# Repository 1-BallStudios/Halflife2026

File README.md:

## Hello!
This is my Starbie.
As the description says, this is "a tiny motion-controlled digital pet, basically a desktop Tamagotchi."

I don't exactly know what to do with how to flash the firmware (**SINCE I DONT HAVE IT YET**), but assembling it should be pretty simple with the parts.

## I'm just using the example because idc
1. Clone the source code to your device
```sh
git clone https://github.com/1-BallStudios/Halflife2026.git
```

2. Install the project's dependencies
```sh
npm install
```

3. Start the development server on `localhost:xxxx`
```sh
npm run dev
```

4. Build the site to `/dist`
```sh
npm run build
```

This project was made almost entirely using the Starbie Week 1 Guide: [Here it is!](https://github.com/SharKingStudios/Starbie/blob/main/Week%201%20Guide.md)
*the thing is... i have almost no idea what im doing. :(* At least I'm learning! :]

## ALSO
When I rendered it, the XIAO-ESPC3 looked fine when I viewed it separately, but in the final render it's not there for some reason. Weird!

# Starbie – bill of materials [PCB Isn't in here]

| Week | Tier | Parts funding |
| --- | --- | --- |
| Week 1 | Tier 1 | $30.00 |

| Part | What it's for | Qty | Unit | Total | Vendor |
| --- | --- | --- | --- | --- | --- |
| [XIAO-ESP32-C3-SMD](https://www.aliexpress.us/item/3256806898073871.html) | Main Microprocessor | 1 | $2.95 | $2.95 | [AliExpress](https://www.aliexpress.us/item/3256806898073871.html) |
| [Push Button Switch](https://www.walmart.com/ip/3x6x3-5mm-Momentary-Tact-Tactile-Push-Button-Switch-Surface-Mounted-Devices-SMT-PCB-2-Pin-50Pcs/922165931?wmlspartner=wlpa&selectedSellerId=571) | Buttons (SORRY THIS IS A 50-PACK) | 2 | $0.44 | $0.88 | [Walmart](https://www.walmart.com/ip/3x6x3-5mm-Momentary-Tact-Tactile-Push-Button-Switch-Surface-Mounted-Devices-SMT-PCB-2-Pin-50Pcs/922165931?wmlspartner=wlpa&selectedSellerId=571) |
| [DHT11 Module](https://www.aliexpress.com/item/32840892862.html) | Enviornment Sensor i think | 1 | $0.44 | $0.44 | [AliExpress](https://www.aliexpress.com/item/32840892862.html) |
| [10kΩ Resistor](https://vetco.net/products/nte-qw310_10k_ohm_1-4_watt_resistor?variant=42879213928585&_gsid=cyqQckRv9BK9) | Resistor | 1 | $0.29 | $0.29 | [Vetco Electronics](https://vetco.net/products/nte-qw310_10k_ohm_1-4_watt_resistor?variant=42879213928585&_gsid=cyqQckRv9BK9) |
| [1.3" OLED Display](https://www.aliexpress.com/item/1005006862867338.html) | Screen | 1 | $0.99 | $0.99 | [AliExpress](https://www.aliexpress.com/item/1005006862867338.html) |
| [MPU6050 Module](https://www.aliexpress.com/w/wholesale-MPU6050.html) | Movement Sensor i think | 1 | $1.09 | $1.09 | [AliExpress](https://www.aliexpress.com/w/wholesale-MPU6050.html) |
| **Parts subtotal** | — | — | — | **$6.64** | — |
| **Tax & shipping** | — | — | — | **$14.27** | — |
| **Total** | — | — | — | **$20.91** | — |

$9.09 left of the tier's funding.

## A.I. DISCLOSURE
I didn't use A.I. for this project. :)

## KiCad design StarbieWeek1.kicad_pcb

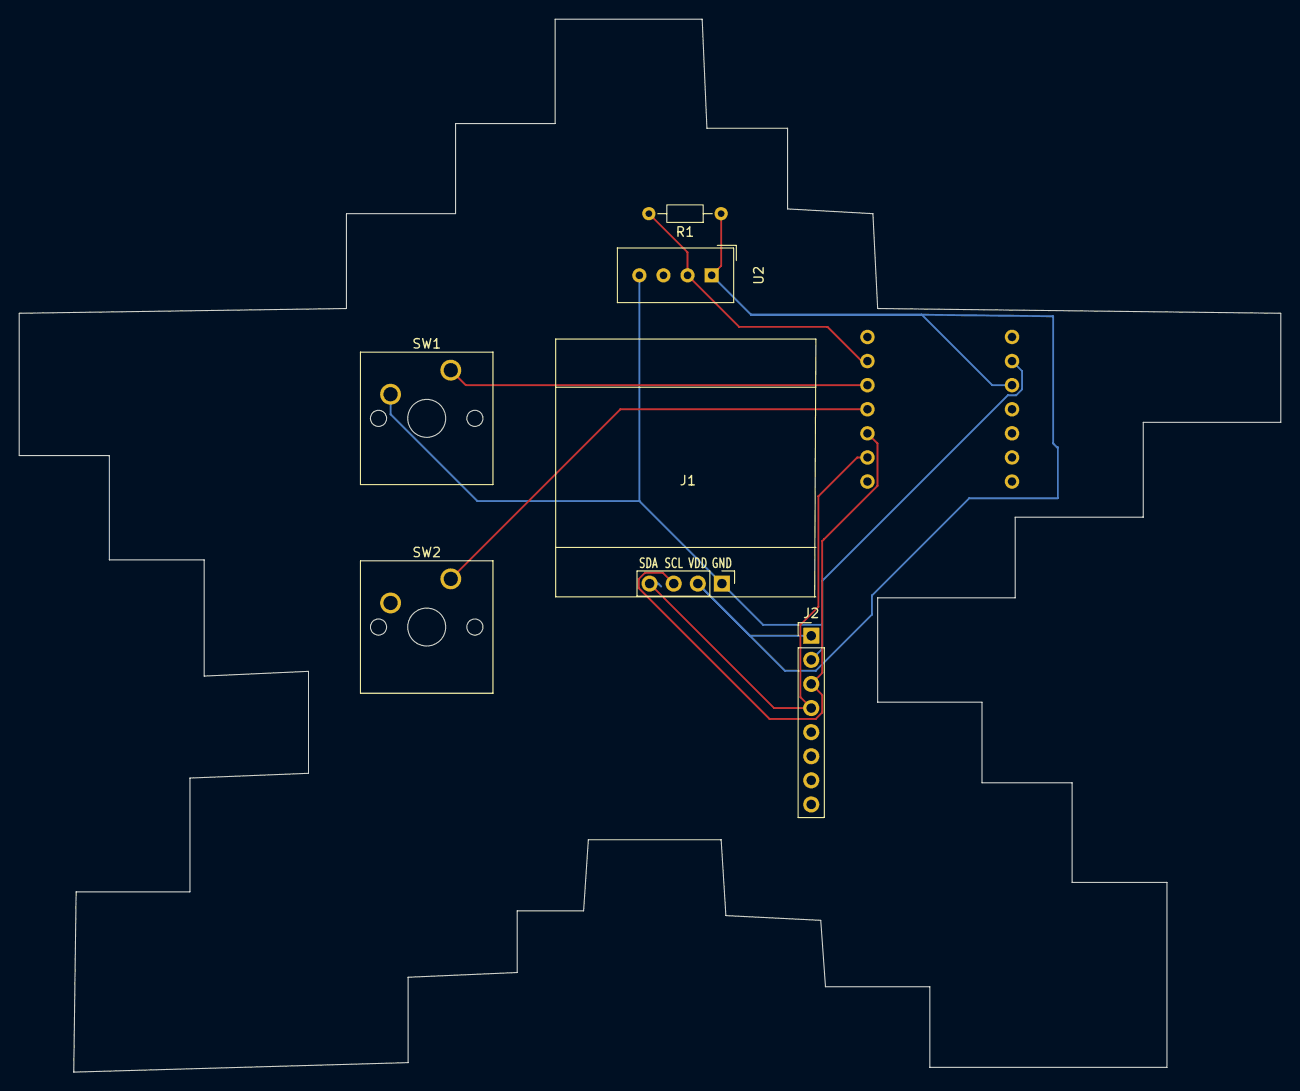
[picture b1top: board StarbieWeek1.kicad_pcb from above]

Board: 2 copper layers, 133.0 x 111.0 mm, 7 parts (1 on the bottom side), 7 nets.

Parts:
J1: Conn_01x04_Pin; Display_128x64_096_I2C
J2: Conn_01x08_Pin; PinHeader_1x08_P2.54mm_Vertical
R1: 10k; R_Axial_DIN0204_L3.6mm_D1.6mm_P7.62mm_Horizontal
SW1, SW2: SW_Push; SW_Cherry_MX_1.00u_PCB
U1: XIAO-ESP32-C3-SMD; XIAO-ESP32-C6-DIP
U2: DHT11; Aosong_DHT11_5.5x12.0_P2.54mm

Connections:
+3.3V: J1.2, J2.1, R1.1, U1.12 (3V3_OUT), U2.1 (VDD)
/DHT11 DATA: R1.2, U1.2 (D1), U2.2 (DATA)
/GPI02: SW1.1, U1.3 (D2)
/GPI03: SW2.1 (1_1), U1.4 (D3)
/SCL: J1.3, J2.3, U1.5 (D4)
/SDA: J1.4, J2.4, U1.6 (D5)
GND: J1.1, J2.2, SW1.2, U1.13 (GND), U2.4 (GND)

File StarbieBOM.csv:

"Reference","Qty","Value","DNP","Exclude from BOM","Exclude from Board","Exclude from Simulation","Exclude from Position Files","Footprint","Datasheet"
"J1","1","Conn_01x04_Pin","","","","","${EXCLUDE_FROM_POS_FILES}","",""
"J2","1","Conn_01x08_Pin","","","","","${EXCLUDE_FROM_POS_FILES}","",""
"R1","1","10k","","","","","${EXCLUDE_FROM_POS_FILES}","",""
"SW1,SW2","2","SW_Push","","","","","${EXCLUDE_FROM_POS_FILES}","",""
"U1","1","XIAO-ESP32-C3-SMD","","","","","${EXCLUDE_FROM_POS_FILES}","Seeed_Studio_XIAO_Series:XIAO-ESP32-C3-SMD",""
"U2","1","DHT11","","","","","${EXCLUDE_FROM_POS_FILES}","Sensor:Aosong_DHT11_5.5x12.0_P2.54mm","http://akizukidenshi.com/download/ds/aosong/DHT11.pdf"
